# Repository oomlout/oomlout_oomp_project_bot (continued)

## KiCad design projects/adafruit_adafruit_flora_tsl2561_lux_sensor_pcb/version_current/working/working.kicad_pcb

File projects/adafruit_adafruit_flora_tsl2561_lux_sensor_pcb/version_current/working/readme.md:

# OOMP Project  
## Adafruit-Flora-TSL2561-Lux-Sensor-PCB  by adafruit  
  
oomp key: oomp_projects_flat_adafruit_adafruit_flora_tsl2561_lux_sensor_pcb  
(snippet of original readme)  
  
-- Adafruit Flora TSL2561 Lux Sensor PCB  
  
<a href="http://www.adafruit.com/products/1246"><br/>  
Click here to purchase one from the Adafruit shop</a>  
  
PCB files for the Adafruit Flora TSL2561 Lux Sensor. Format is EagleCAD schematic and board layout  
* https://www.adafruit.com/product/1246  
  
--- DESCRIPTION  
Add light-reactive sensing to your wearable Flora project with this high precision Lux sensor. The TSL2561 luminosity sensor is an advanced digital light sensor, ideal for use in a wide range of light situations. Compared to low cost CdS cells, this sensor is more precise, allowing for exact lux calculations and can be configured for different gain/timing ranges to detect light ranges from up to 0.1 - 40,000+ Lux on the fly. The best part of this sensor is that it contains both infrared and full spectrum diodes! That means you can separately measure infrared, full-spectrum or human-visible light. Most sensors can only detect one or the other, which does not accurately represent what human eyes see (since we cannot perceive the IR light that is detected by most photo diodes)  
  
The sensor has a digital (I2C) interface. Attaching it to the flora is simple: line up the sensor so its adjacent to the SDA/SCL pins and sew conductive thread from the 3V, SDA, SCL and GND pins. They line up perfectly so you will not have any crossed lines. You can only connect one lux sensor to your Flora, but you can connect other I2C sensors/outputs   
  full source readme at [readme_src.md](readme_src.md)  
  
source repo at: [https://github.com/adafruit/Adafruit-Flora-TSL2561-Lux-Sensor-PCB](https://github.com/adafruit/Adafruit-Flora-TSL2561-Lux-Sensor-PCB)  
## Board  

## Schematic  

[schematic pdf](working_schematic.pdf)  
## Images

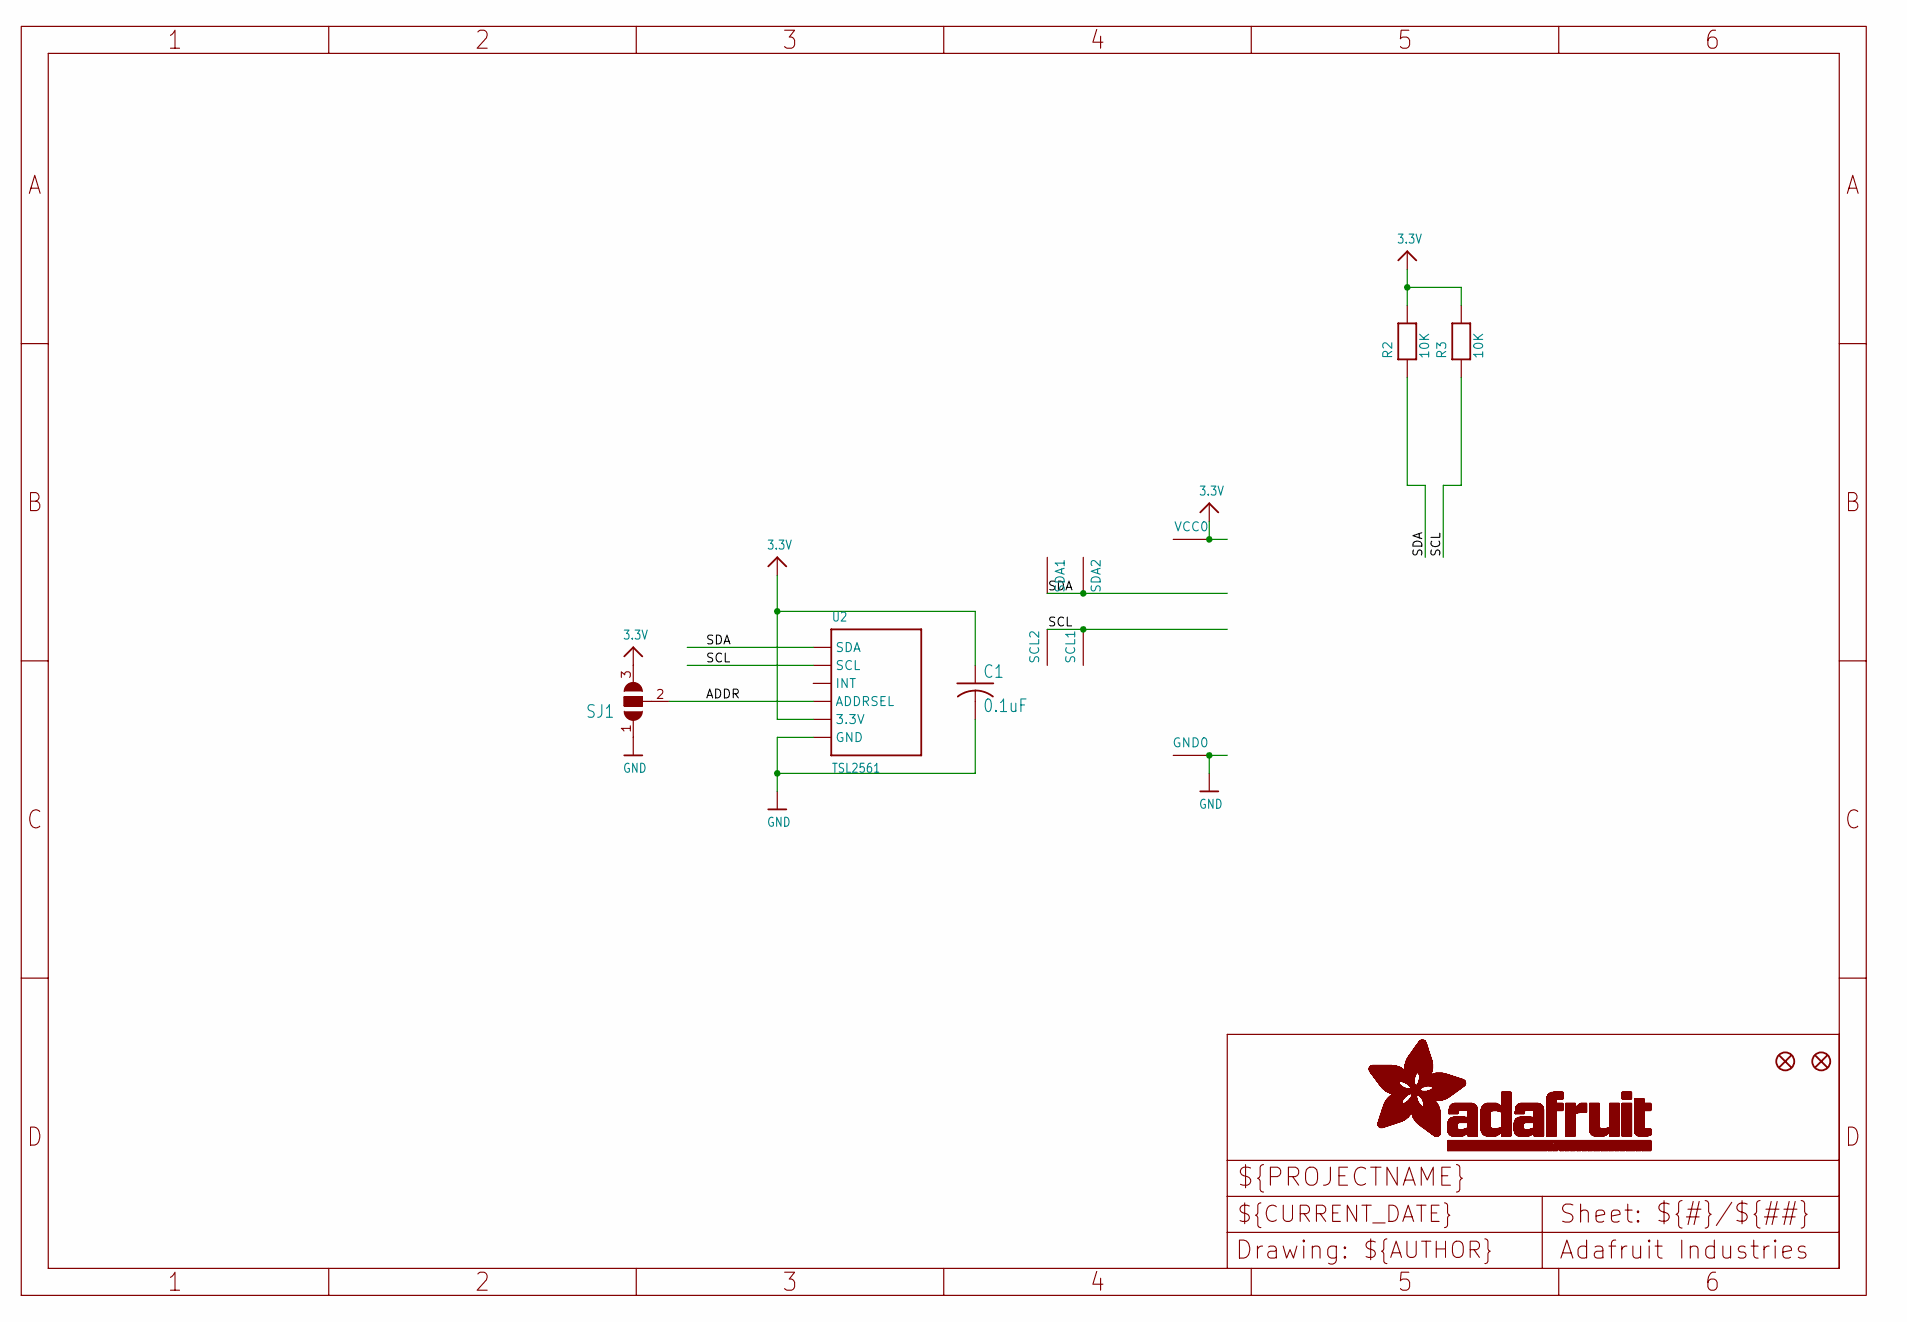
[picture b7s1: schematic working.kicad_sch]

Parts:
C1: 0.1uF; C0805K
FID1, FID2: FIDUCIAL""; FIDUCIAL_1MM
GND0: SEWTAP0.5IN; SEWINGTAP_0.5
R2, R3: 10K; _0805
SCL1, SCL2: SEWTAP0.5IN; SEWINGTAP_0.5
SDA1, SDA2: SEWTAP0.5IN; SEWINGTAP_0.5
SJ1: SJ2W; SJ_2
U2: TSL2561; TSL2561_FN
VCC0: SEWTAP0.5IN; SEWINGTAP_0.5

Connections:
3.3V: C1.1, R2.2, R3.2, SJ1.3, U2.VDD (3.3V), VCC0.TAP
ADDR: SJ1.2, U2.ADR (ADDRSEL)
GND: C1.2, GND0.TAP, SJ1.1, U2.VSS (GND)
SCL: R3.1, SCL1.TAP, SCL2.TAP, U2.CLK (SCL)
SDA: R2.1, SDA1.TAP, SDA2.TAP, U2.DATA (SDA)

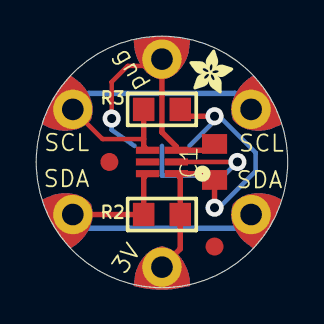
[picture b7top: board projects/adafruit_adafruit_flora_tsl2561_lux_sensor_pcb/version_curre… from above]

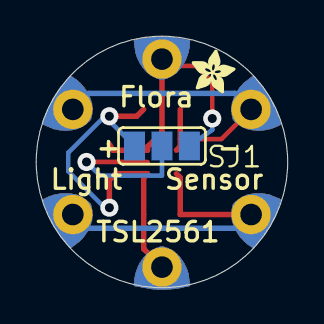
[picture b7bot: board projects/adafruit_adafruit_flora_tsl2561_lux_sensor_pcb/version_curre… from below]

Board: 2 copper layers, 14.0 x 14.0 mm, 15 parts (2 on the bottom side), 5 nets.

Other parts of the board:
U$3, U$4: ADAFRUIT_2.5MM

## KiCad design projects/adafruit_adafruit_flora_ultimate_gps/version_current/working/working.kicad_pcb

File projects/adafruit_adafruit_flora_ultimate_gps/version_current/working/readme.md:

# OOMP Project  
## Adafruit-Flora-Ultimate-GPS  by adafruit  
  
oomp key: oomp_projects_flat_adafruit_adafruit_flora_ultimate_gps  
(snippet of original readme)  
  
- PCB for the Adafruit Flora Ultimate GPS  
  
<a href="http://www.adafruit.com/products/1059"><br/>Click here to purchase one from the Adafruit shop</a>  
  
__Format is EagleCAD schematic and board layout__  
  
This module is the best way to add a GPS to your wearable project. It's part of the Adafruit Flora series of wearable electronics, designed specifically for use with the Flora motherboard. Installed on the PCB is the latest of our Ultimate GPS modules, a small, super-thin, low power GPS module with built in data-logging capability! This module's easy to use, but extremely powerful:  
  
- -165 dBm sensitivity, 10 Hz updates, 66 channels  
- Designed for wearable use with the Flora system  
- Only 20mA current draw  
- RTC battery-compatible - sew a battery on to create a atomic-precision real time clock  
- Built-in datalogging  
- Internal patch antenna + u.FL connector for external active antenna  
- Fix status LED  
  
...all for under $40!  
  
The breakout is built around the MTK3339 chipset, a no-nonsense, high-quality GPS module that can track up to 22 satellites on 66 channels, has an excellent high-sensitivity receiver (-165 dB tracking!), and a built in antenna. It can do up to 10 location updates a second for high speed, high sensitivity logging or tracking. Power usage is incredibly low, only 20 mA during navigation.  
  
The module is kept small and simple, we have a ferrite bead, filter capacitor and red fix LED on board. The LED blinks at a  
  full source readme at [readme_src.md](readme_src.md)  
  
source repo at: [https://github.com/adafruit/Adafruit-Flora-Ultimate-GPS](https://github.com/adafruit/Adafruit-Flora-Ultimate-GPS)  
## Board  

## Schematic  

[schematic pdf](working_schematic.pdf)  
## Images

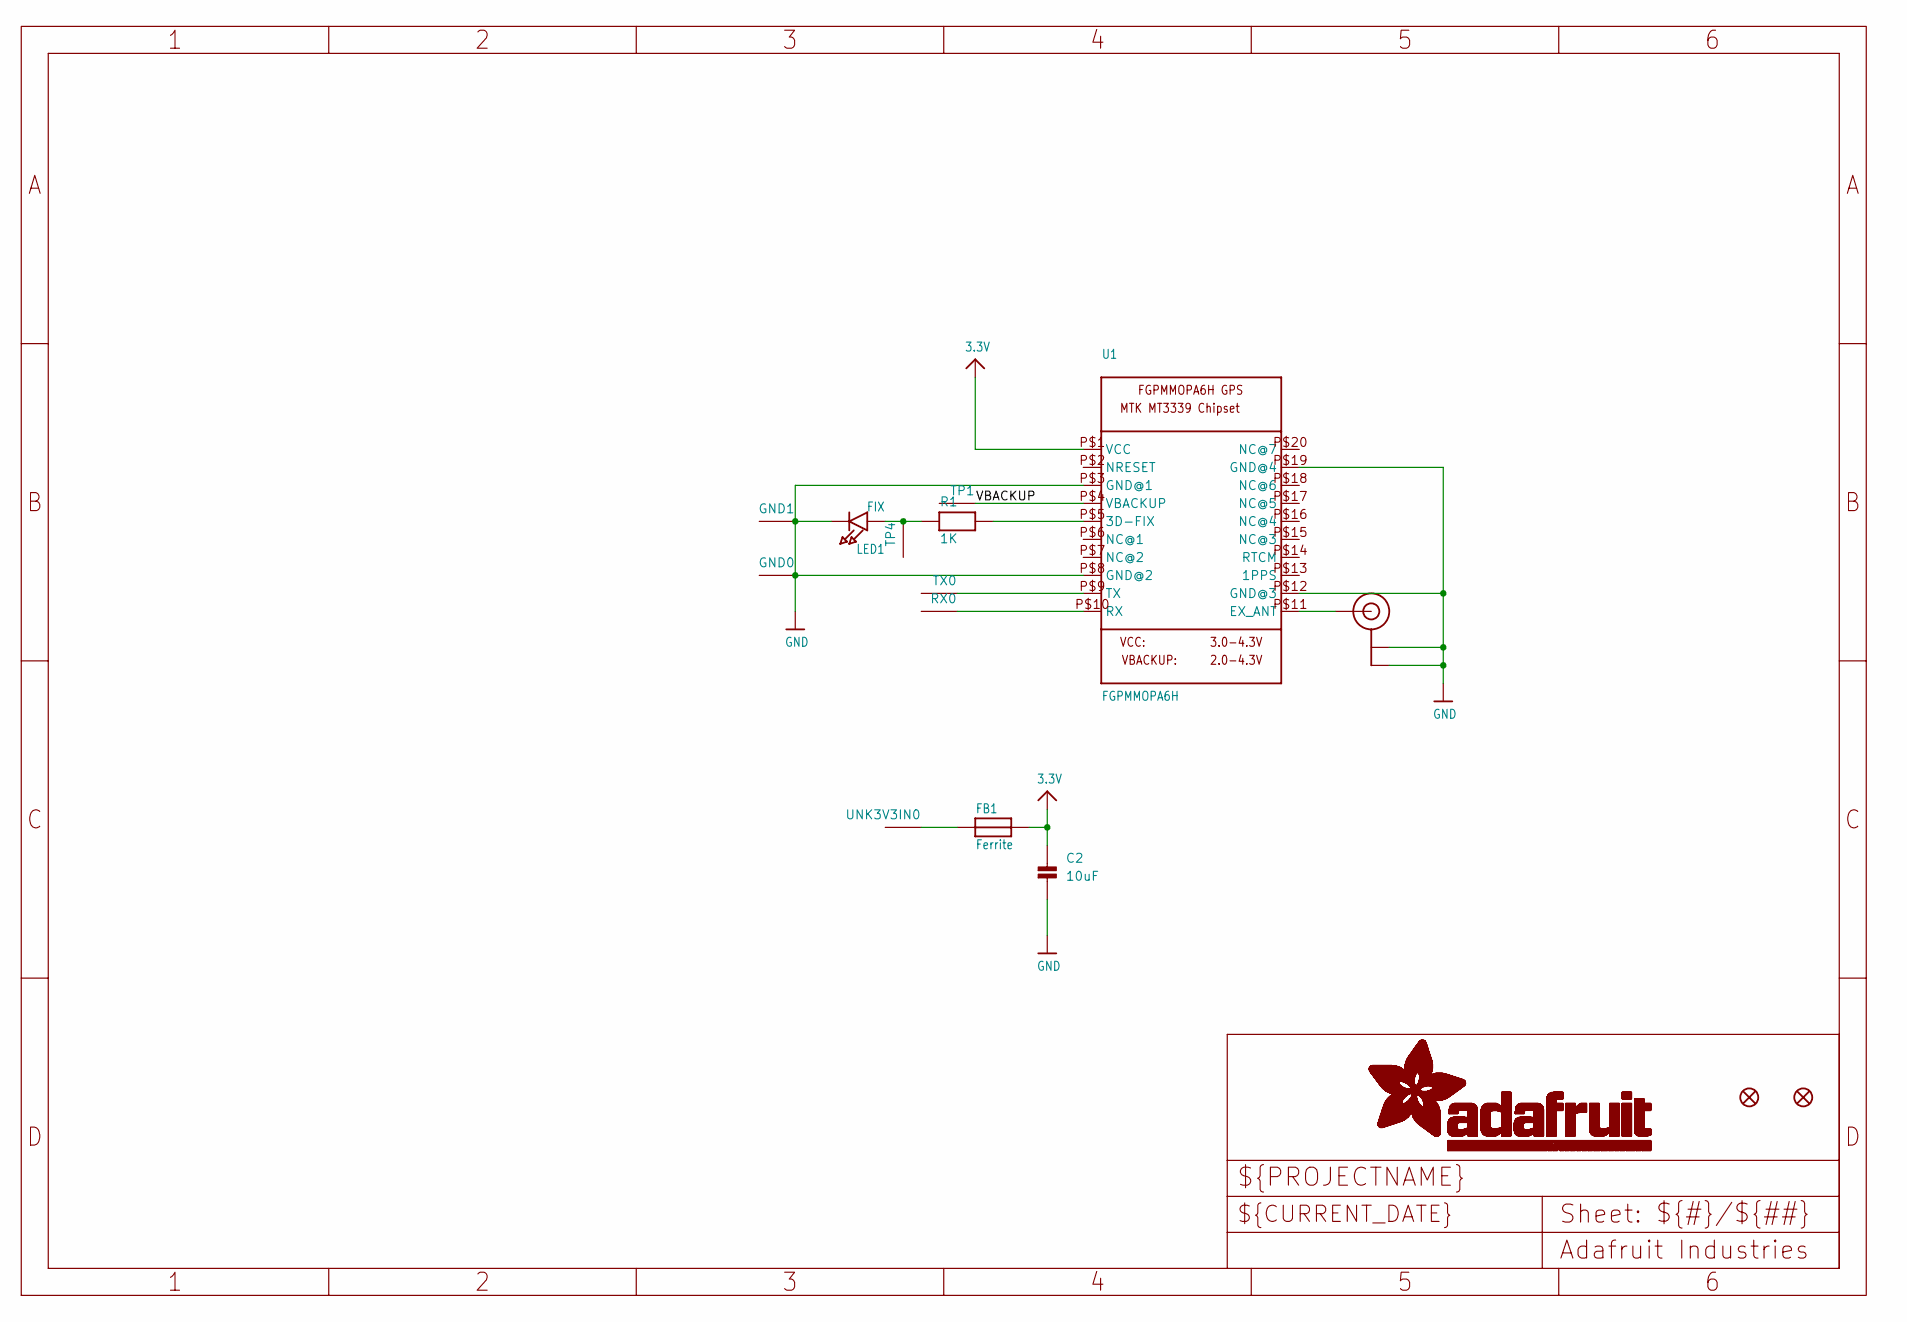
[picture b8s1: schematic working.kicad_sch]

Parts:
C2: 10uF; 0805
FB1: Ferrite; 0805
FID1, FID2: FIDUCIAL""; FIDUCIAL_1MM
GND0, GND1: SEWTAP-2.0IN; SEWINGTAP_2.0
LED1: FIX; CHIPLED_0805
R1: 1K; 0805
RX0: SEWTAP-2.0IN; SEWINGTAP_2.0
TP1, TP4: SEWTAP-2.0IN; SEWINGTAP_2.0
TX0: SEWTAP-2.0IN; SEWINGTAP_2.0
U1: FGPMMOPA6H
U$20: U.FL
UNK3V3IN0: SEWTAP-2.0IN; SEWINGTAP_2.0

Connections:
3.3V: C2.1, FB1.2, U1.P$1 (VCC)
GND: C2.2, GND0.P$1, GND1.P$1, LED1.C, U1.P$3 (GND@1), U1.P$8 (GND@2), U1.P$12 (GND@3), U1.P$19 (GND@4), U$20.P$1 (GND@0), U$20.P$2 (GND@1)
unnamed: LED1.A, R1.1, TP4.P$1
unnamed: R1.2, U1.P$5 (3D-FIX)
unnamed: FB1.1, UNK3V3IN0.P$1
unnamed: U1.P$11 (EX_ANT), U$20.P$3 (SIGNAL)
RX: RX0.P$1, U1.P$10 (RX)
TX: TX0.P$1, U1.P$9 (TX)
VBACKUP: TP1.P$1, U1.P$4 (VBACKUP)

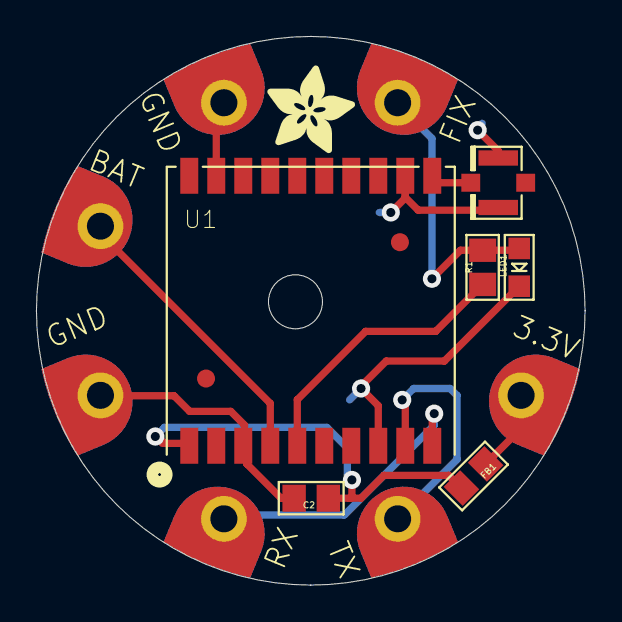
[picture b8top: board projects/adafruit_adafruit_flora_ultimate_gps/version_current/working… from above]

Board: 2 copper layers, 30.5 x 30.5 mm, 17 parts (1 on the bottom side), 9 nets.

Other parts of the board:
U$6: ADAFRUIT_5MM
U$7: FLORASMALL
